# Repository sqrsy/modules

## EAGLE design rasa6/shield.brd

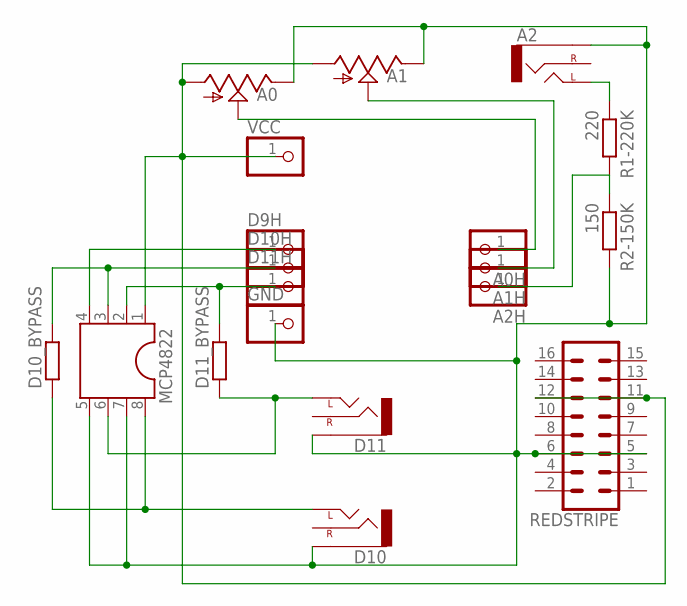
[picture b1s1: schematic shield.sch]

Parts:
A0, A1: 9MM_SNAP-IN_POT_; 9MM_SNAP-IN_POT
A0H, A1H, A2H: PINHD-1X1; 1X01
A2: THONKI-STEREO; WQP-PJ366ST_JACK
D9H, D10H, D11H: PINHD-1X1; 1X01
D10, D11: THONKI-STEREO; WQP-PJ366ST_JACK
D10_BYPASS, D11_BYPASS: RESISTOR10MM_RESISTOR; 10MM_RESISTOR
GND: PINHD-1X1; 1X01
MCP4822: DIL8; DIL08
R1-220K: 220; 7MM_RESISTOR
R2-150K: 150; 7MM_RESISTOR
REDSTRIPE: CONN_08X2; 2X8
VCC: PINHD-1X1; 1X01

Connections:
unnamed: D10.P$1_TIP (LEFT), D10_BYPASS.1, MCP4822.8
unnamed: D11.P$1_TIP (LEFT), D11_BYPASS.1, MCP4822.6
unnamed: A0.3 (E), A1.3 (E), A2.P$3_SLEEVE (SLEEVE), D10.P$3_SLEEVE (SLEEVE), D11.P$3_SLEEVE (SLEEVE), GND.1, MCP4822.5, MCP4822.7, R2-150K.2, REDSTRIPE.5, REDSTRIPE.6
unnamed: D9H.1, MCP4822.4
unnamed: A2.P$1_TIP (LEFT), R1-220K.1
unnamed: A0.1 (A), A1.1 (A), MCP4822.1, REDSTRIPE.11, REDSTRIPE.12, VCC.1
unnamed: A2H.1, R1-220K.2, R2-150K.1
unnamed: A1.2 (S), A1H.1
unnamed: A0.2 (S), A0H.1
unnamed: D11H.1, D11_BYPASS.2, MCP4822.2
unnamed: D10H.1, D10_BYPASS.2, MCP4822.3

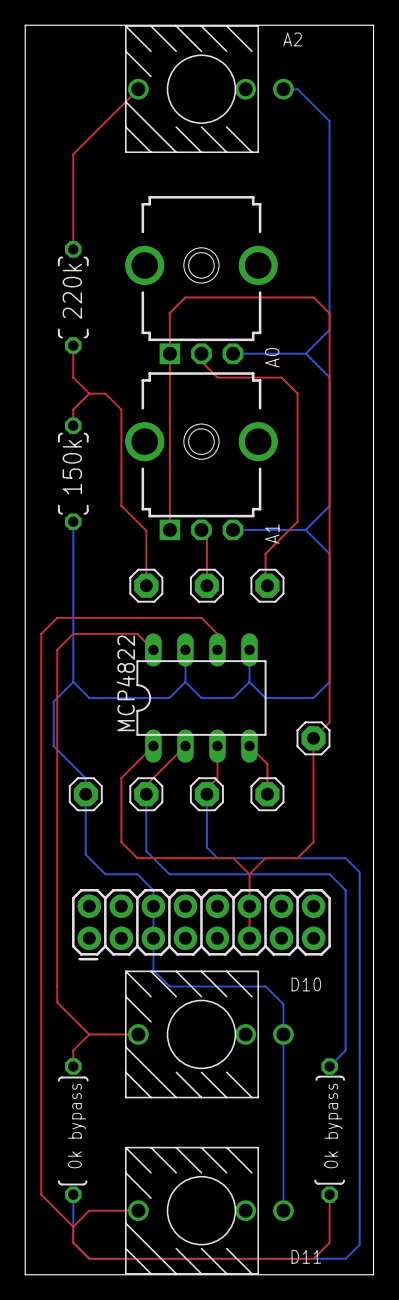
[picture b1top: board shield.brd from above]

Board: 2 copper layers, 27.6 x 99.0 mm, 19 parts (0 on the bottom side), 11 nets.

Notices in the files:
parts and their libraries:
SparkFun-Connectors: Licensing: Creative Commons ShareAlike 4.0 International - https://creativecommons.org/licenses/by-sa/4.0
